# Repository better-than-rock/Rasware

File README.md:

Rasware
=======

Description
-----------

Rasware is a generic robotics library project for the EK-LM4F120XL Stellaris Launchpad, built on top of StellarisWare. It is intended to be used for UT RAS's Robotathon competition as well as general purpose robotics projects.
Authored by the IEEE - Robotics and Automation Society Student Branch at the University of Texas at Austin. For documentation, see Rasware's Github [wiki](https://github.com/ut-ras/Rasware/wiki).

Robotathon Setup Instructions
-----------------------------

### Get started with Git ###
1. Create a free GitHub account on [github.com](https://github.com/signup/free)
3. If you want to learn more about Git check out this great beginners guide http://rogerdudler.github.io/git-guide/ or if you really want to get into it, you can read the GitPro book online for free (and legally, too!) at http://git-scm.com/book

### Fork Rasware (only one Robotathon team member should do this step) ###
1. Once logged into GitHub, go to [ut-ras](https://github.com/ut-ras)'s [Rasware](https://github.com/ut-ras/Rasware).
2. [Fork](https://help.github.com/articles/fork-a-repo) the project's code through the button on the top right. This will copy the project to your own account.
3. On the team's forked repository Github page, go to `Settings -> Collaborators` and add each team member as a collaborator

The remainder of the instructions will depend on what type of system you're running. 

Setup for Windows (with VMware)
-------------------------------
### Install VMware ###
1. Download and install [VMware Workstation Player](https://my.vmware.com/web/vmware/downloads) (near the bottom of the page).
2. WMware Player is a hypervisor that lets us run a controlled environment for writing and flashing code.
3. Download a copy of the latest Ubuntu LTS .iso from here:

    64-bit: ftp://ftp.utexas.edu/pub/ubuntu-iso/16.04.3/ubuntu-16.04.3-desktop-amd64.iso
    
    32-bit: ftp://ftp.utexas.edu/pub/ubuntu-iso/16.04.3/ubuntu-16.04.3-desktop-i386.iso
4. Open VMWare and select Create a New Virtual Machine.
5. Select the Installer disc image file bubble and navigate to your freshly downloaded .iso. Click next.
6. Full Name is your own name. User name is whatever you want, all lower case, no special characters. Create and confirm a password. Click next.
7. Choose a name for your VM. (Some people like to theme their Linux machine names. We've seen famous scientists, video game AIs, Star Trek starship classes, whatever you want.)
8. Make sure you're okay with the location where you'll store this machine, then click next.
9. 20GB is a good max disk size. This will not immediately allocate 20GB, it will be populated as you fill it. This is just the max allowed size.
10. Store your virtual disk as a single file. Click next.
11. Click Customize Hardware, then slide the memory slider up to 4GB. This is plenty of RAM for this VM's purposes. Click close.
12. Click finish, let the machine install, then log in!
    
    If VMWare complains about VT-x not being enabled, you'll need to go through your BIOS and enable VT-x. There should in instructions in the dialog box.

### Forward USB ###
1. Plug in a Launchpad to your computer. If you don't have a Launchpad available this step can be done later.
2. In the VM, select `Player -> Removable Devices -> Luminary Micro ICDI` and select `Connect`.

### Jump to the Linux Instructions ###
1. Follow the rest of the instructions on how to use Rasware from the [Install Dependencies](#install-dependencies-1) step in the Linux instructions.

Setup for Mac
-------------

### Install Dependencies ###
0. Before we do anything else, run this in your terminal if you're running Marericks or newer (macOS 10.9+) and haven't already done this:

  ```bash
        xcode-select --install
  ```

1. Install Homebrew: [link](http://brew.sh) (Installation instructions are at the bottom of the page.)
2. Install OpenOCD through Homebrew in a terminal.

  ```bash
    brew install openocd
  ```

3. Install the Cross Compiler Toolchain for Embedded ARM Devices through Homebrew as well:

  ```bash
        brew cask install gcc-arm-embedded
  ```

### Configure Groups ###
1. On macOS devices belong to the `wheel` group, so in order to access the devices on your Mac (like the Launchpad) you also need to be part of the `wheel` group. Put the following in a terminal to see what groups you're part of:

  ```bash
      groups
  ```

2. If `wheel` was one of the groups listed, you're good to go and can skip the next step.

3. If not, add yourself to the `wheel` group:

  ```bash
    sudo dscl . append /Groups/wheel GroupMembership $(whoami)
  ```

### Jump to the Linux Instructions ###
1. If everything has worked so far, follow the rest of the instructions on how to use Rasware from the [setup a directory](#setup-a-directory) step in the Linux instructions.

Setup for Linux
---------------
These instructions are written for use in a terminal (xterm, gterm, kterm, tty1, etc.) and assume that you have already installed, and are familiar with, your favorite text editor. If you have not found a favorite text editor, I recomend you take a look at [Vim](http://www.vim.org), [Emacs](http://www.emacswiki.org/emacs/), and [SublimeText3](http://www.sublimetext.com/).

### Install Dependencies ###
1. First install the basic dependencies
* Archlinux : `sudo pacman -S git base-devel openocd screen arm-none-eabi-gcc arm-none-eabi-gdb arm-none-eabi-newlib`
* Ubuntu/Debian : `sudo apt-get install git build-essential openocd screen gcc-arm-none-eabi gdb-arm-none-eabi libnewlib-arm-none-eabi`

### Setup a Directory ###
1. Create a directory to work in. This is where we will place everything.

  ```bash
    mkdir ras
    cd ras
  ```

### Clone Rasware ###
Use git to clone Rasware, *replacing "username" with your Git username in the URL.* Make sure you've forked Rasware already!
This makes a copy of Rasware on your computer.

  ```bash
    git clone https://github.com/username/Rasware.git
  ```

### Download StellarisWare ###
1. Locate Stellarisware, the TI library, in Rasware/Downloads on your computer (in the repository you cloned).
2. Uncompress the file, compile StellarisWare, and move it to `/usr/local/lib`.

  ```bash
    tar vfx StellarisWare.tar.bz2
    cd StellarisWare
    make
    cd ..
    sudo mv StellarisWare /usr/local/lib
    rm StellarisWare.tar.bz2
  ```

### Add the LM4F rule to UDev ###
#### (skip this step if you're on macOS) ####
1. To avoid needing root access to communicate with the lm4f, you will need to copy the lm4f rule to the udev directory.

  ```bash
    wget https://raw.githubusercontent.com/ut-ras/Rasware/master/RASLib/51-lm4f.rules
    sudo mv 51-lm4f.rules /etc/udev/rules.d
  ```

2. Trigger udev for the new rules to come into effect.

  ```bash
    sudo udevadm control --reload
    sudo udevadm trigger
  ```

3. Plug in a Stellaris Launchpad. you should now see the file `/dev/lm4f`.

### Compile Rasware, RASTemplate, RASDemo ###
Compile RASLib by using the [make](<https://en.wikipedia.org/wiki/Make_(software)>) program.

  ```bash
    cd Rasware/RASLib
    make
    cd ..
    cd RASTemplate
    make
    cd ..
    cd RASDemo
    make
  ```

### Compile and run RASDemo ###
1. We have created an example project to demonstrate Rasware running on a Launchpad.
2. Compile RASDemo.

  ```bash
    cd Rasware/RASDemo
    make
  ```

3. To flash RASDemo to the board, we use make with different arguments.

  ```bash
    make flash
  ```
  If you get an Error 1, `make flash` again and make sure your USB device is connected, powered on, and forwarded to your VM if necessary. If you see "shutdown command invoked," press the reset button. This will start the program on your launchpad. If you keep getting Error 1's, make sure you've forwarded your LaunchPad's USB connection to the VM: In the VM, select `Player -> Removable Devices -> Luminary Micro ICDI` and select `Connect`.
  
  Else, if at this point an error message is printed that includes "Error erasing flash with vFlashErase packet", run the following command twice and press the board's reset button:
  ```bash
    openocd -f $(find /usr -path */scripts/board/*tm4c123* 2>/dev/null) -c init -c halt -c "flash write_image erase RASDemo.out" -c verify_image RASDemo.out -c halt -c shutdown
  ```
  You should now be able to use `make flash` normally until you flash from Keil again. Keil seems to break things. Thank you to Kevin George for this workaround.

4. If a launchpad is plugged in, it should be accessible at a special file in `/dev` (`/dev/lm4f` on Linux, `/dev/tty.usbmodem[board's serial id]` on macOS - run the detect-board script in the RASLib folder if you're curious). You can use make to create a terminal over [UART](https://en.wikipedia.org/wiki/Universal_asynchronous_receiver/transmitter).

  ```bash
    make uart
  ```

5. You should now be presented with the RASDemo menu. Feel free to mess around and look into RASDemo's source code to see how it is done. To exit press `C-a d`, or control-A followed by a d. This will detach the launchpad's UART from your current console. To get back to the launchpad, in your console run `screen -r`.

6. If you don't want to do all of the above steps each time, you can run everything with one command.

  ```bash
    make run
  ```
  
 However, please note openeing the console may give an error if the command was already run before and was detached. If this happens, try running `screen -r` in console.

### Committing code back to your repo ###
1. Before you start, you should configure git with both your username and email.

  ```bash
    git config --global user.name "User Name"
    git config --global user.email "your@email.here"
  ```

2. Git will keep track of any changes to your directory. You can use the status command to show the state of git.

  ```bash
    git status
  ```

3. To track a file, you can use the add command.

  ```bash
    git add filename
  ```

4. You can now use the commit command to create a commit containing all of the modifications of the files you `git add`ed. It will open an editor for writing a [commit message](https://github.com/erlang/otp/wiki/Writing-good-commit-messages). If saved, the commit will be created.

  ```bash
    git commit
  ```

5. To move your local changes to the server, use the push command.

  ```bash
    git push origin master
  ```

### Fin ###

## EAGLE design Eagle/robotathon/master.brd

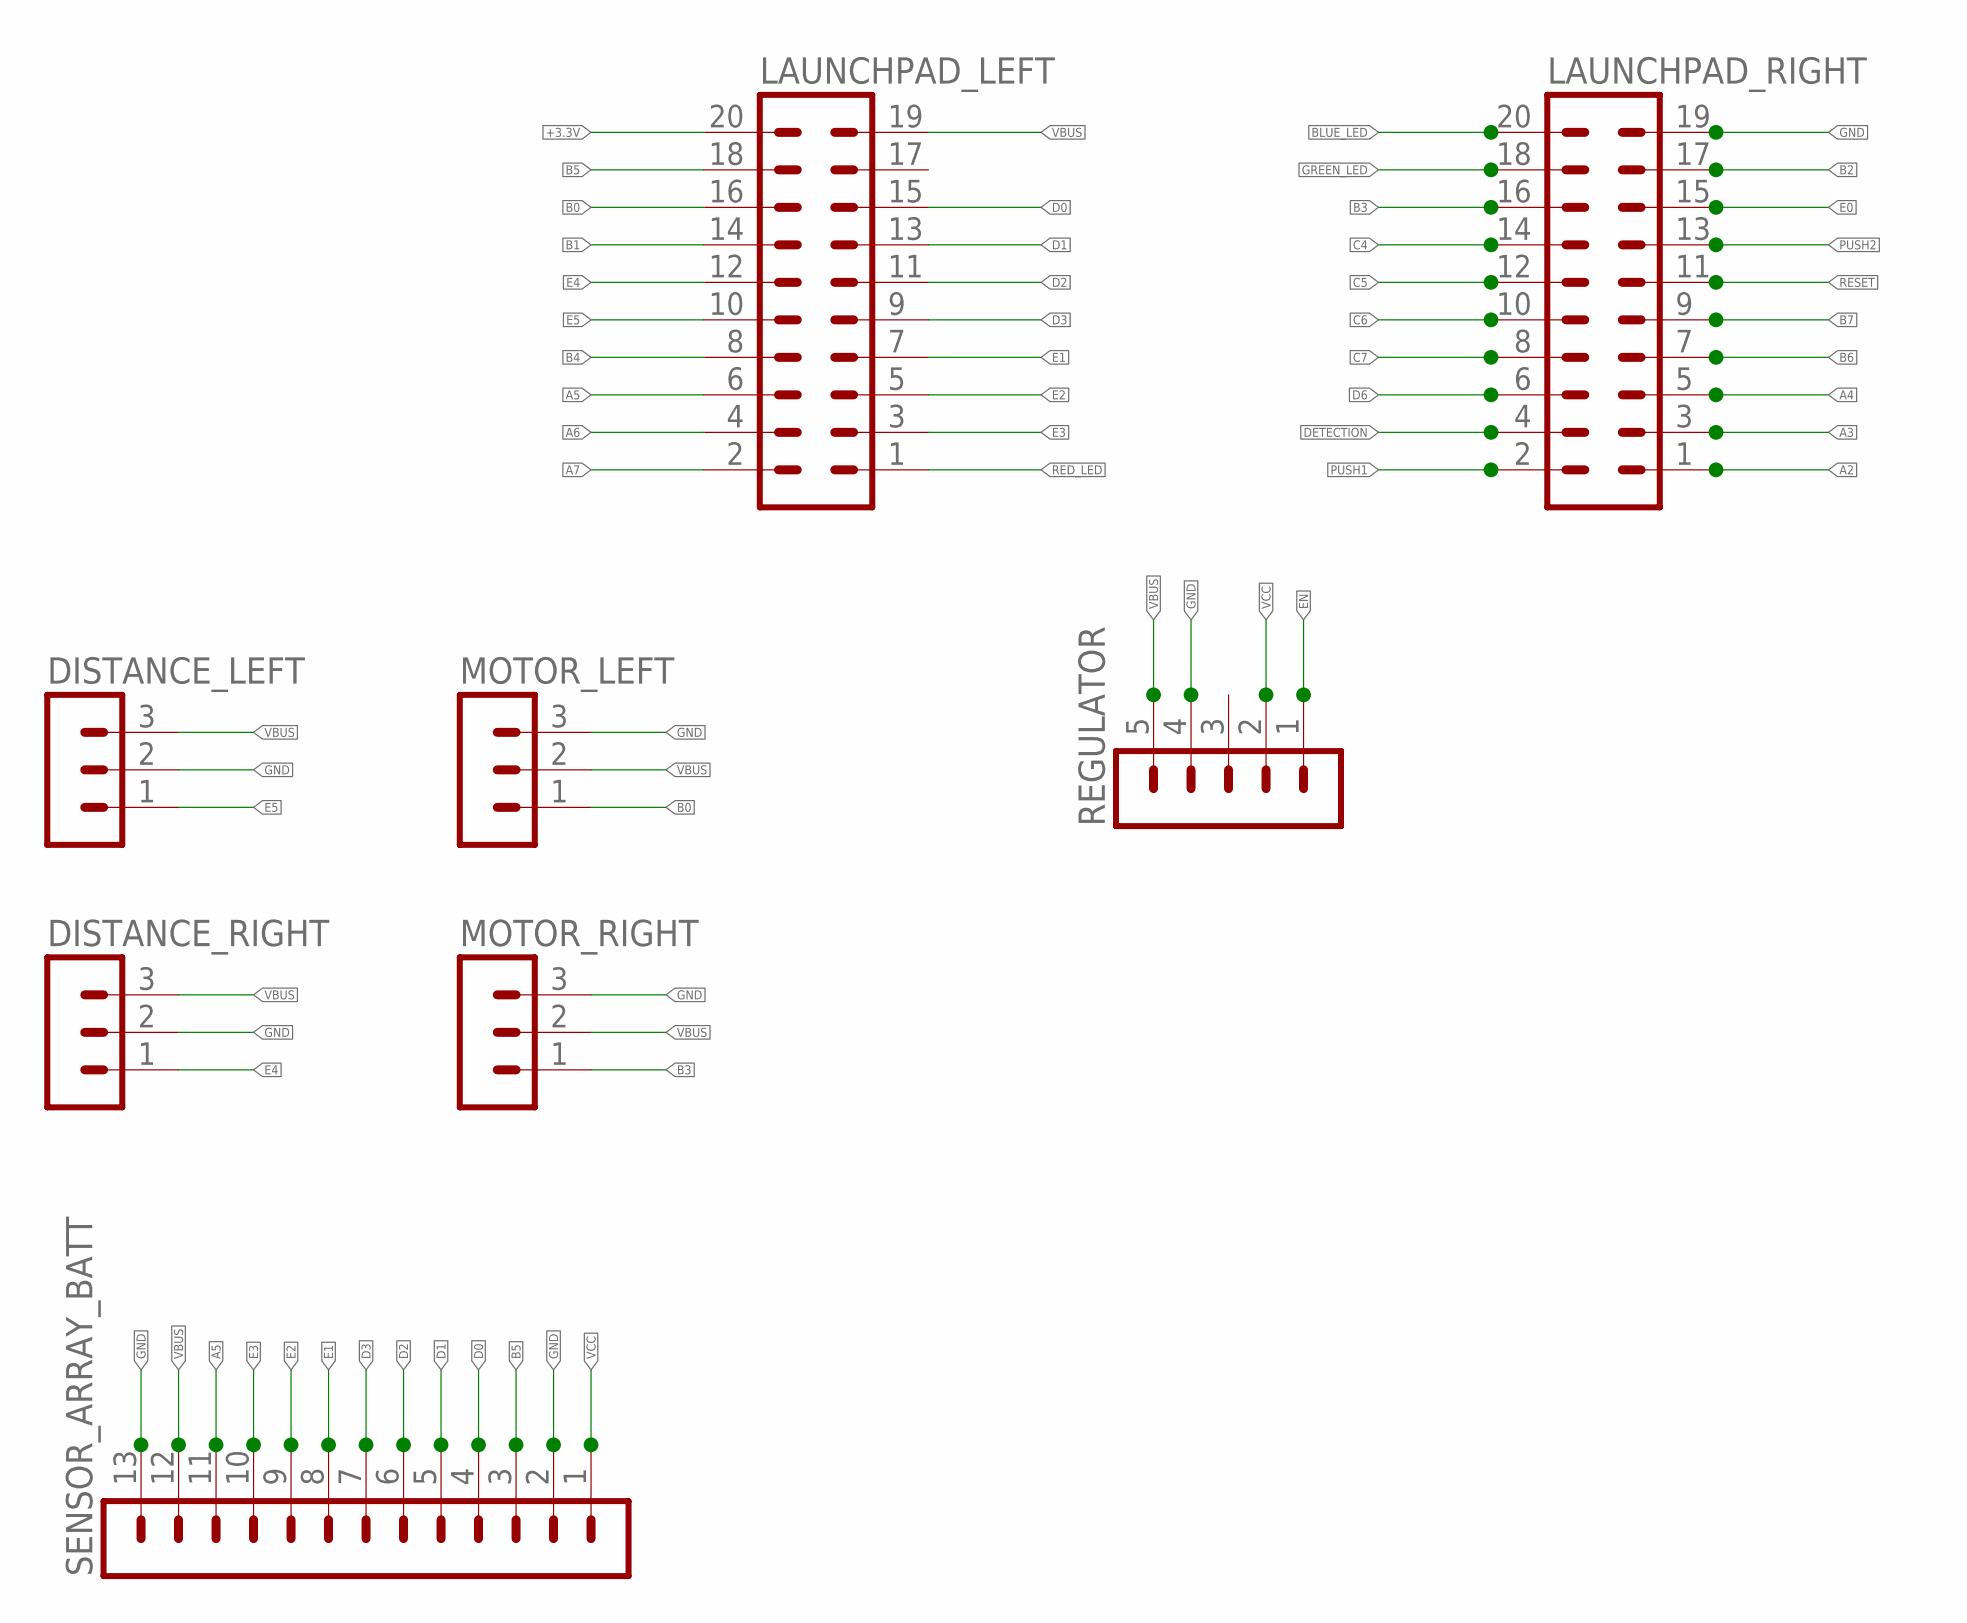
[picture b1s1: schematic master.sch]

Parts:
DISTANCE_LEFT: MA03-1
DISTANCE_RIGHT: MA03-1
LAUNCHPAD_LEFT: MA10-2
LAUNCHPAD_RIGHT: MA10-2
MOTOR_LEFT: MA03-1
MOTOR_RIGHT: MA03-1
REGULATOR: MA05-1
SENSOR_ARRAY_BATT: MA13-1

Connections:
+3.3V: LAUNCHPAD_LEFT.20
A2: LAUNCHPAD_RIGHT.1
A3: LAUNCHPAD_RIGHT.3
A4: LAUNCHPAD_RIGHT.5
A5: LAUNCHPAD_LEFT.6, SENSOR_ARRAY_BATT.11
A6: LAUNCHPAD_LEFT.4
A7: LAUNCHPAD_LEFT.2
B0: LAUNCHPAD_LEFT.16, MOTOR_LEFT.1
B1: LAUNCHPAD_LEFT.14
B2: LAUNCHPAD_RIGHT.17
B3: LAUNCHPAD_RIGHT.16, MOTOR_RIGHT.1
B4: LAUNCHPAD_LEFT.8
B5: LAUNCHPAD_LEFT.18, SENSOR_ARRAY_BATT.3
B6: LAUNCHPAD_RIGHT.7
B7: LAUNCHPAD_RIGHT.9
BLUE_LED: LAUNCHPAD_RIGHT.20
C4: LAUNCHPAD_RIGHT.14
C5: LAUNCHPAD_RIGHT.12
C6: LAUNCHPAD_RIGHT.10
C7: LAUNCHPAD_RIGHT.8
D0: LAUNCHPAD_LEFT.15, SENSOR_ARRAY_BATT.4
D1: LAUNCHPAD_LEFT.13, SENSOR_ARRAY_BATT.5
D2: LAUNCHPAD_LEFT.11, SENSOR_ARRAY_BATT.6
D3: LAUNCHPAD_LEFT.9, SENSOR_ARRAY_BATT.7
D6: LAUNCHPAD_RIGHT.6
DETECTION: LAUNCHPAD_RIGHT.4
E0: LAUNCHPAD_RIGHT.15
E1: LAUNCHPAD_LEFT.7, SENSOR_ARRAY_BATT.8
E2: LAUNCHPAD_LEFT.5, SENSOR_ARRAY_BATT.9
E3: LAUNCHPAD_LEFT.3, SENSOR_ARRAY_BATT.10
E4: DISTANCE_RIGHT.1, LAUNCHPAD_LEFT.12
E5: DISTANCE_LEFT.1, LAUNCHPAD_LEFT.10
EN: REGULATOR.1
GND: DISTANCE_LEFT.2, DISTANCE_RIGHT.2, LAUNCHPAD_RIGHT.19, MOTOR_LEFT.3, MOTOR_RIGHT.3, REGULATOR.4, SENSOR_ARRAY_BATT.2, SENSOR_ARRAY_BATT.13
GREEN_LED: LAUNCHPAD_RIGHT.18
PUSH1: LAUNCHPAD_RIGHT.2
PUSH2: LAUNCHPAD_RIGHT.13
RED_LED: LAUNCHPAD_LEFT.1
RESET: LAUNCHPAD_RIGHT.11
VBUS: DISTANCE_LEFT.3, DISTANCE_RIGHT.3, LAUNCHPAD_LEFT.19, MOTOR_LEFT.2, MOTOR_RIGHT.2, REGULATOR.5, SENSOR_ARRAY_BATT.12
VCC: REGULATOR.2, SENSOR_ARRAY_BATT.1

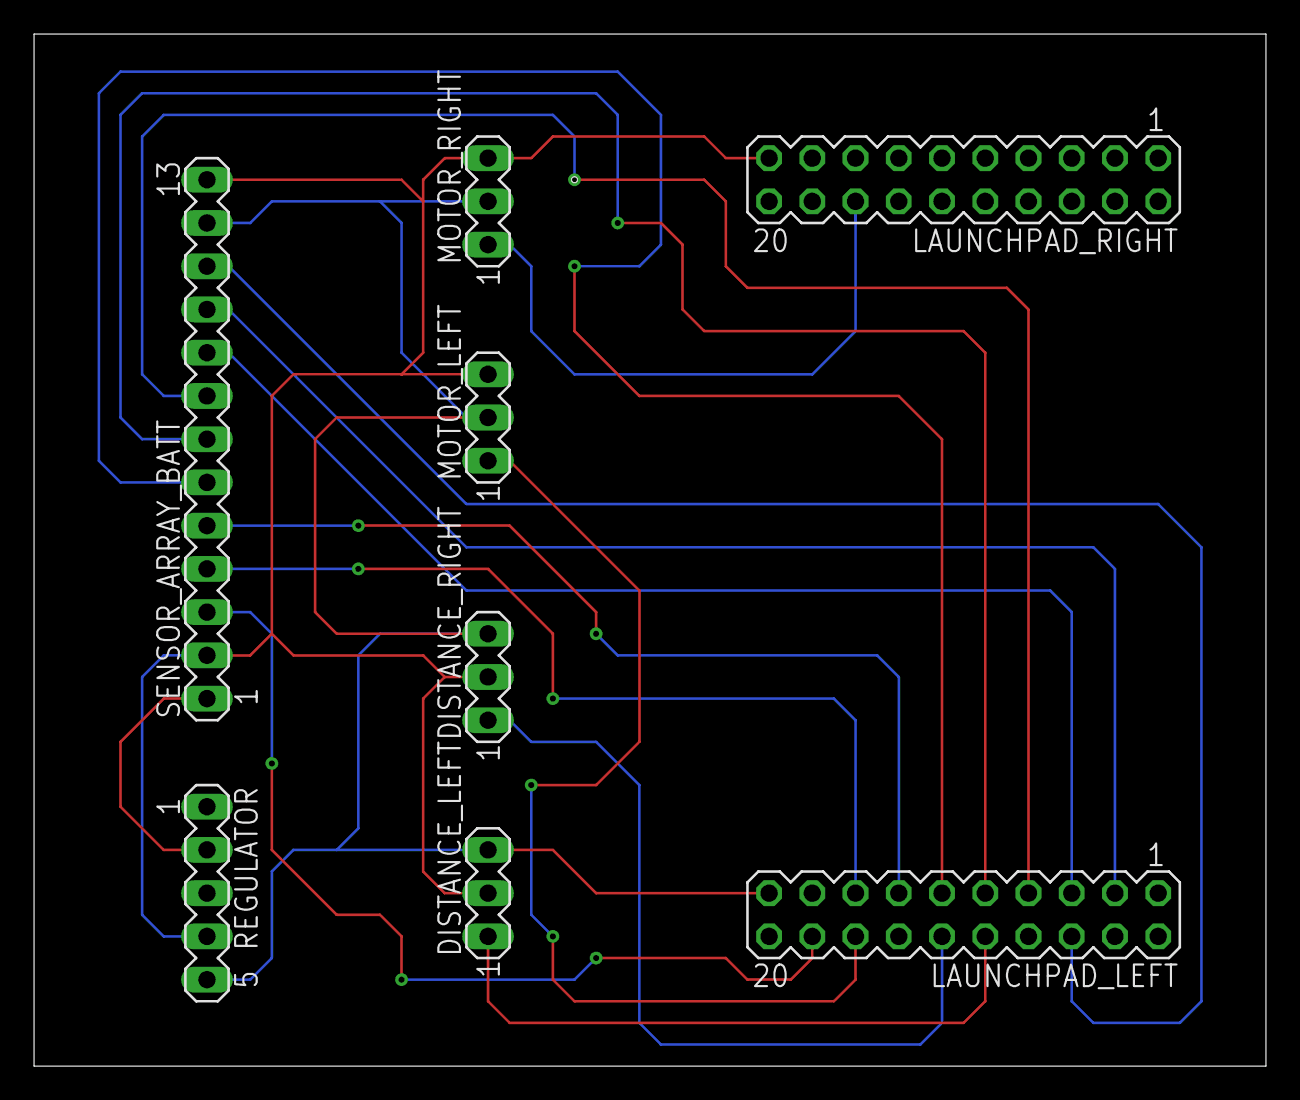
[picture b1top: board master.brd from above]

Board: 2 copper layers, 72.4 x 60.6 mm, 8 parts (0 on the bottom side), 16 nets.

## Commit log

2017-10-09 Added BTR Folder and removed temp files
2017-10-16 Motor Code for moving base
2017-10-19 copied corban's code
2017-10-19 Using other folder
2017-10-23 Added eagle files
2017-10-24 Fixed Kim's mess
2017-10-24 Added eagle stuff
2017-10-24 Fixed main func
2017-10-24 Debug code for the IR sensors
2017-10-24 Adjusted pins for sensors
2017-10-24 Added debug for distance sensor
2017-10-24 Trying a different appraoch
2017-10-28 Code for checkpoint
2017-10-28 Cleaned up files
2017-11-07 Improved readability of the Main.c and prepared for line following
2017-11-10 started working on line following
2017-11-10 Working on debugigng
2017-11-13 Adapted code and refactored wall following.
2017-11-13 Updated readme to clear up some things
2017-11-13 Fixed formatting
2017-11-13 Added more info on git
2017-11-14 Removed junk files
2017-11-14 removed outdated stuff
2017-11-15 Updated something
2017-11-15 Ignore Line Following
2017-11-15 Changed 100 to 5
2017-11-15 Added drastic wall change
2017-11-15 Disabled turning
2017-11-18 Added checking for no line
